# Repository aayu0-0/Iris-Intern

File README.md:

# Autonomous System Development Platform 🚀  
**AI-Driven Intelligence • Embedded Control • Custom Hardware**

---

## Project Overview  
This repository represents a **complete autonomous system prototype**, developed as a multidisciplinary engineering project integrating **Artificial Intelligence**, **embedded firmware**, **custom PCB hardware**, **application-level UI/UX**, and **mechanical enclosure design**.

The project was executed in a **team-based environment (5 members)** with a strong focus on real-world system design practices, including modular architecture, hardware–software co-design, and scalable development.

The aim was not only to build a functional autonomous system, but to design it the way **industry-grade autonomous platforms** are actually engineered.

---

## Vision & Motivation 🌍  
Autonomous systems are complex cyber-physical products that require seamless interaction between:

- Intelligent decision-making algorithms  
- Real-time embedded control  
- Robust and reliable custom electronics  
- Human–machine interaction interfaces  
- Mechanical protection and form factor design  

This project was initiated to **bridge the gap between theoretical knowledge and practical system deployment**, simulating a real product development workflow from concept to prototype.

---

## Key Objectives 🎯  

- Design a **modular and scalable autonomous system architecture**
- Develop **AI/ML-based perception and decision-making**
- Implement **embedded firmware** for real-time system control
- Design a **custom prototype PCB** tailored to system requirements
- Build an **application-level UI/UX** for monitoring and interaction
- Design a **mechanical casing** using SolidWorks for physical deployment
- Practice **technical leadership, system integration, and documentation**

---

## System Architecture 🧩  

The system is divided into well-defined layers that work together as a single autonomous platform:

1. **AI / ML Layer**  
   Handles perception, inference, and high-level decision-making.

2. **Firmware Layer**  
   Responsible for sensor interfacing, actuator control, communication protocols, and real-time execution.

3. **Hardware Layer (PCB)**  
   Custom-designed PCB providing power management, signal routing, and peripheral integration.

4. **Application Layer (UI/UX)**  
   User interface for system monitoring, control, and configuration  
   *(Completed – pending upload to repository)*

5. **Mechanical Design Layer**  
   SolidWorks-designed casing for protection, mounting, and usability  
   *(Completed – pending upload to repository)*

---

## Technologies & Tools 🛠️  

- **AI / ML:** Python, machine learning libraries  
- **Embedded Firmware:** C / C++  
- **PCB Design:** KiCad  
- **UI / UX Application:** Application-based monitoring & control *(completed)*  
- **Mechanical Design:** SolidWorks *(completed)*  
- **Version Control:** Git & GitHub  

---

## Development Status 🚧  

| Module | Status |
|------|-------|
| AI / ML | Implemented |
| Firmware | Implemented |
| PCB Design | Prototype completed |
| System Integration | Completed |
| UI / UX Application | Completed |
| Mechanical Casing | Completed |

---

## Why This Project Matters 💡  
This project demonstrates a **full autonomous system engineering pipeline**, covering:

- Multidisciplinary technical depth  
- Hardware–software co-design  
- Leadership and system ownership  
- Product-oriented engineering mindset  

It reflects the skills required for **industry-level autonomous systems, robotics, and embedded product development**.

---

## Future Enhancements 🔮  
- PCB revision based on extended testing and optimization  
- Performance tuning of AI models  
- System robustness and reliability testing  
- Deployment-focused refinements  

---

## Acknowledgements  
This project was developed as a collaborative team effort, with clearly defined roles and shared responsibility for successful system delivery.

---

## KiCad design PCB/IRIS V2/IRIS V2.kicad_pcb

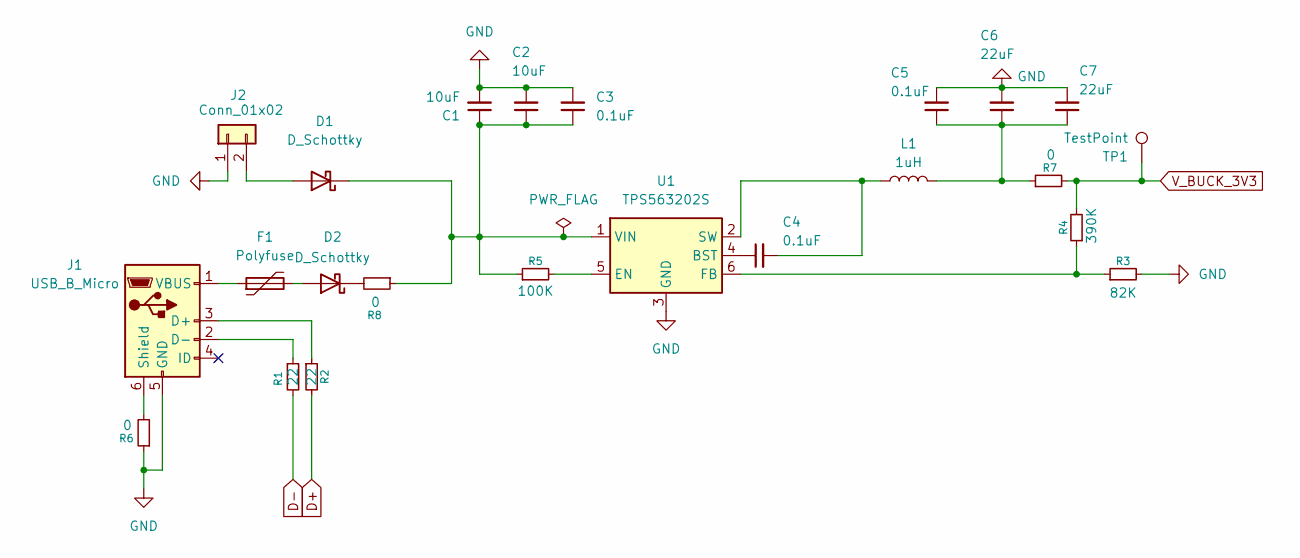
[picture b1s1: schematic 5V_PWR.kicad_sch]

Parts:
C1, C2: 10uF; C_1206_3216Metric
C3, C4, C5: 0.1uF; C_1206_3216Metric
C6, C7: 22uF; C_1206_3216Metric
D1, D2: D_Schottky; D_DO-15_P10.16mm_Horizontal
F1: Polyfuse; Fuse_Littelfuse-LVR100
J1: USB_B_Micro; USB_Micro-B_GCT_USB3076-30-A
J2: Conn_01x02; JST_XH_B2B-XH-A_1x02_P2.50mm_Vertical
L1: 1uH; L_6.3x6.3_H3
R1, R2: 22; R_1206_3216Metric
R3: 82K; R_1206_3216Metric
R4: 390K; R_1206_3216Metric
R5: 100K; R_1206_3216Metric
R6, R7, R8: 0; R_1206_3216Metric
TP1: TestPoint; TestPoint_Pad_1.0x1.0mm
U1: TPS563202S; SOT-563

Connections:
D+: R2.2; also elsewhere on the board
D-: R1.2; also elsewhere on the board
GND: C1.2, C2.2, C3.2, C5.2, C6.2, C7.2, J1.5 (GND), J2.1, R3.2, R6.1, U1.3 (GND); also elsewhere on the board
unnamed: C5.1, C6.1, C7.1, L1.2, R7.1
unnamed: D1.2 (A), J2.2
unnamed: C1.1, C2.1, C3.1, D1.1 (K), R5.1, R8.1, U1.1 (VIN)
unnamed: D2.2 (A), F1.2
unnamed: D2.1 (K), R8.2
unnamed: J1.3 (D+), R2.1
unnamed: J1.2 (D-), R1.1
unnamed: J1.6 (Shield), R6.2
unnamed: F1.1, J1.1 (VBUS)
unnamed: C4.1, U1.4 (BST)
unnamed: R5.2, U1.5 (EN)
unnamed: R3.1, R4.1, U1.6 (FB)
unnamed: C4.2, L1.1, U1.2 (SW)
V_BUCK_3V3: R4.2, R7.2, TP1.1; also elsewhere on the board

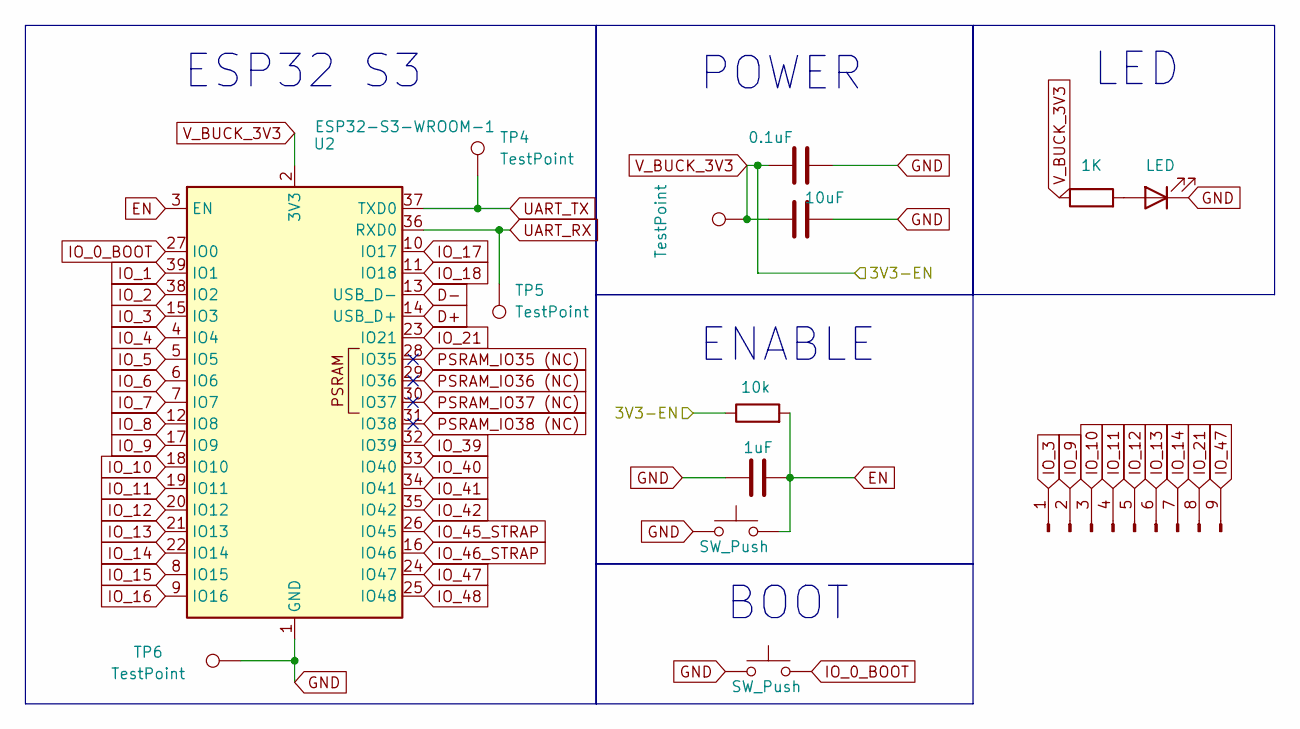
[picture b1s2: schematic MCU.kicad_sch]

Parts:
C9: 10uF; C_1206_3216Metric
C10: 1uF; C_1206_3216Metric
C11: 0.1uF; C_1206_3216Metric
D3: LED; LED_1206_3216Metric_Pad1.42x1.75mm_HandSolder
J4: Conn_01x09_Pin; PinHeader_1x09_P2.54mm_Vertical
R10: 10k; R_1206_3216Metric
R11: 1K; R_1206_3216Metric
SW1, SW2: SW_Push; SW_PUSH_6mm
TP4, TP5, TP6, TP7: TestPoint; TestPoint_Pad_1.0x1.0mm
U2: ESP32-S3-WROOM-1

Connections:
CS: U2.39 (IO1); also elsewhere on the board
D+: U2.14 (USB_D+); also elsewhere on the board
D-: U2.13 (USB_D-); also elsewhere on the board
EN: C10.1, R10.2, SW1.2, U2.3 (EN)
GND: C9.2, C10.2, C11.2, D3.1 (K), SW1.1, SW2.1, TP6.1, U2.1 (GND), U2.40 (GND), U2.41 (GND); also elsewhere on the board
IO_0_BOOT: SW2.2, U2.27 (IO0)
IO_2: U2.38 (IO2); also elsewhere on the board
IO_3: J4.1, U2.15 (IO3)
IO_4: U2.4 (IO4)
IO_5: U2.5 (IO5)
IO_6: U2.6 (IO6)
IO_7: U2.7 (IO7)
IO_8: U2.12 (IO8)
IO_9: J4.2, U2.17 (IO9)
IO_10: J4.3, U2.18 (IO10)
IO_11: J4.4, U2.19 (IO11)
IO_12: J4.5, U2.20 (IO12)
IO_13: J4.6, U2.21 (IO13)
IO_14: J4.7, U2.22 (IO14)
IO_15: U2.8 (IO15)
IO_16: U2.9 (IO16)
IO_17: U2.10 (IO17)
IO_18: U2.11 (IO18)
IO_21: J4.8, U2.23 (IO21)
IO_39: U2.32 (IO39); also elsewhere on the board
IO_40: U2.33 (IO40); also elsewhere on the board
IO_41: U2.34 (IO41); also elsewhere on the board
IO_42: U2.35 (IO42); also elsewhere on the board
IO_45_STRAP: U2.26 (IO45)
IO_46_STRAP: U2.16 (IO46)
IO_47: J4.9, U2.24 (IO47)
IO_48: U2.25 (IO48); also elsewhere on the board
unnamed: D3.2 (A), R11.2
PSRAM_IO35 (NC): U2.28 (IO35)
PSRAM_IO36 (NC): U2.29 (IO36)
PSRAM_IO37 (NC): U2.30 (IO37)
PSRAM_IO38 (NC): U2.31 (IO38)
UART_RX: TP5.1, U2.36 (RXD0)
UART_TX: TP4.1, U2.37 (TXD0)
V_BUCK_3V3: C9.1, C11.1, R10.1, R11.1, TP7.1, U2.2 (3V3); also elsewhere on the board

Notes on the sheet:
ESP32 S3
POWER
ENABLE
BOOT
LED

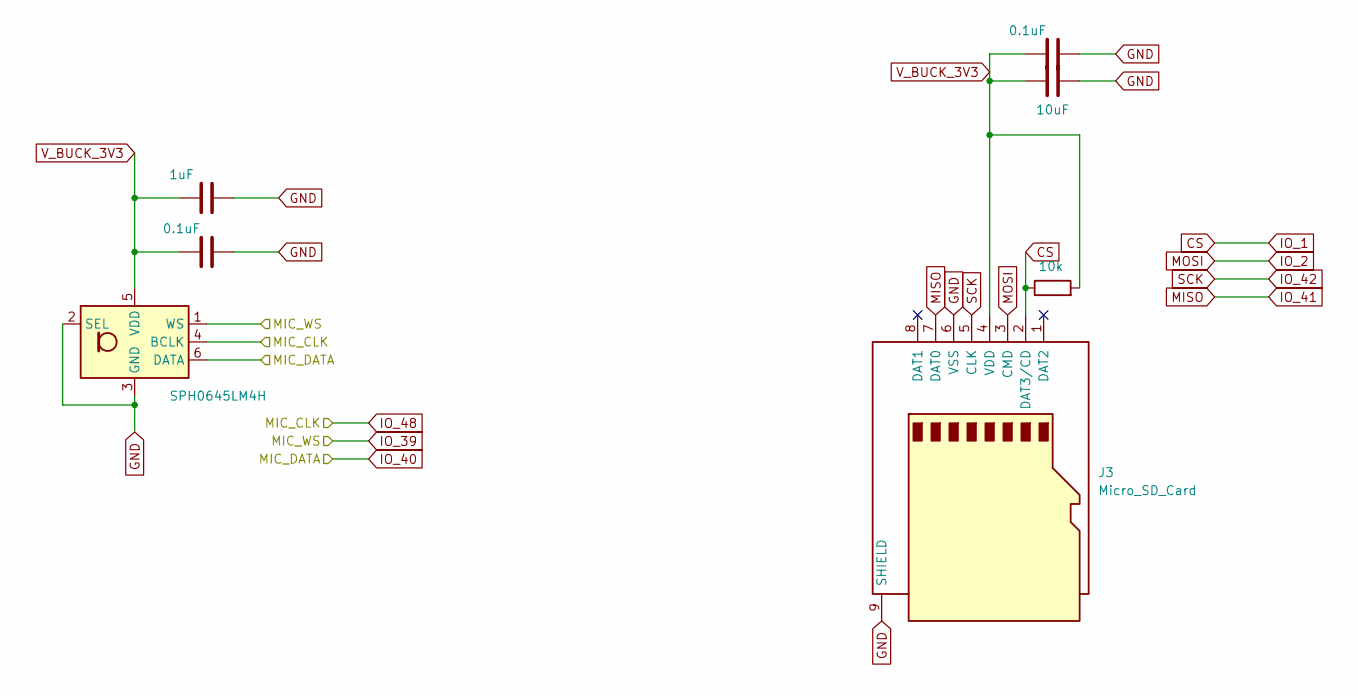
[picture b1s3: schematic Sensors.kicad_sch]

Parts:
C8, C13: 0.1uF; C_1206_3216Metric
C12: 1uF; C_1206_3216Metric
C14: 10uF; C_1206_3216Metric
J3: Micro_SD_Card; microSD_HC_Hirose_DM3D-SF
MK1: SPH0645LM4H; Knowles_SPH0645LM4H-6_3.5x2.65mm
R13: 10k; R_1206_3216Metric

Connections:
CS: J3.2 (DAT3/CD), R13.1; also elsewhere on the board
GND: C8.2, C12.2, C13.2, C14.2, J3.6 (VSS), J3.9 (SHIELD), MK1.2 (SEL), MK1.3 (GND); also elsewhere on the board
IO_2: J3.3 (CMD); also elsewhere on the board
IO_39: MK1.1 (WS); also elsewhere on the board
IO_40: MK1.6 (DATA); also elsewhere on the board
IO_41: J3.7 (DAT0); also elsewhere on the board
IO_42: J3.5 (CLK); also elsewhere on the board
IO_48: MK1.4 (BCLK); also elsewhere on the board
V_BUCK_3V3: C8.1, C12.1, C13.1, C14.1, J3.4 (VDD), MK1.5 (VDD), R13.2; also elsewhere on the board

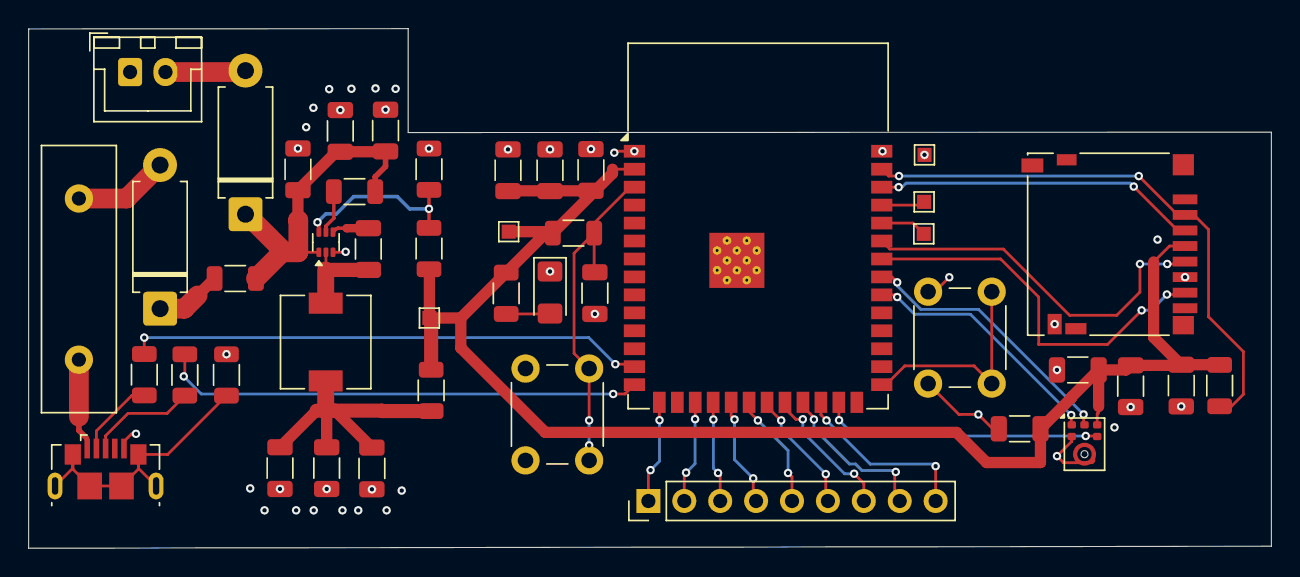
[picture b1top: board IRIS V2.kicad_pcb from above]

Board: 2 copper layers, 87.9 x 36.8 mm, 45 parts (0 on the bottom side), 38 nets.

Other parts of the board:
C8#2: 0.1uF; C_1206_3216Metric

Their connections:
GND: C8#2.2; also elsewhere on the board
V_BUCK_3V3: C8#2.1; also elsewhere on the board

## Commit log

2026-02-10 Initial project upload
2026-02-10 Move firmware code into firmware/ directory
2026-02-10 AI_ML based repo push
2026-02-10 Update requirements.txt file
2026-02-10 Enhance README with project details and structure
    Added comprehensive project overview, objectives, system architecture, technologies used, development status, and future enhancements to the README.
2026-02-10 Initial commit: IRIS landing page
2026-02-10 Clean main branch: restore original README and move landing page into subfolder
2026-02-11 Create ui-ux
2026-02-11 Create README.md for UI/UX designs
    Added README.md to document UI/UX designs for the Iris project.
2026-02-11 Update README with new screen references
    Added Voice Chat and Home Assistant screens to the README.
2026-02-11 Fix formatting for Voice Chat Screen link
